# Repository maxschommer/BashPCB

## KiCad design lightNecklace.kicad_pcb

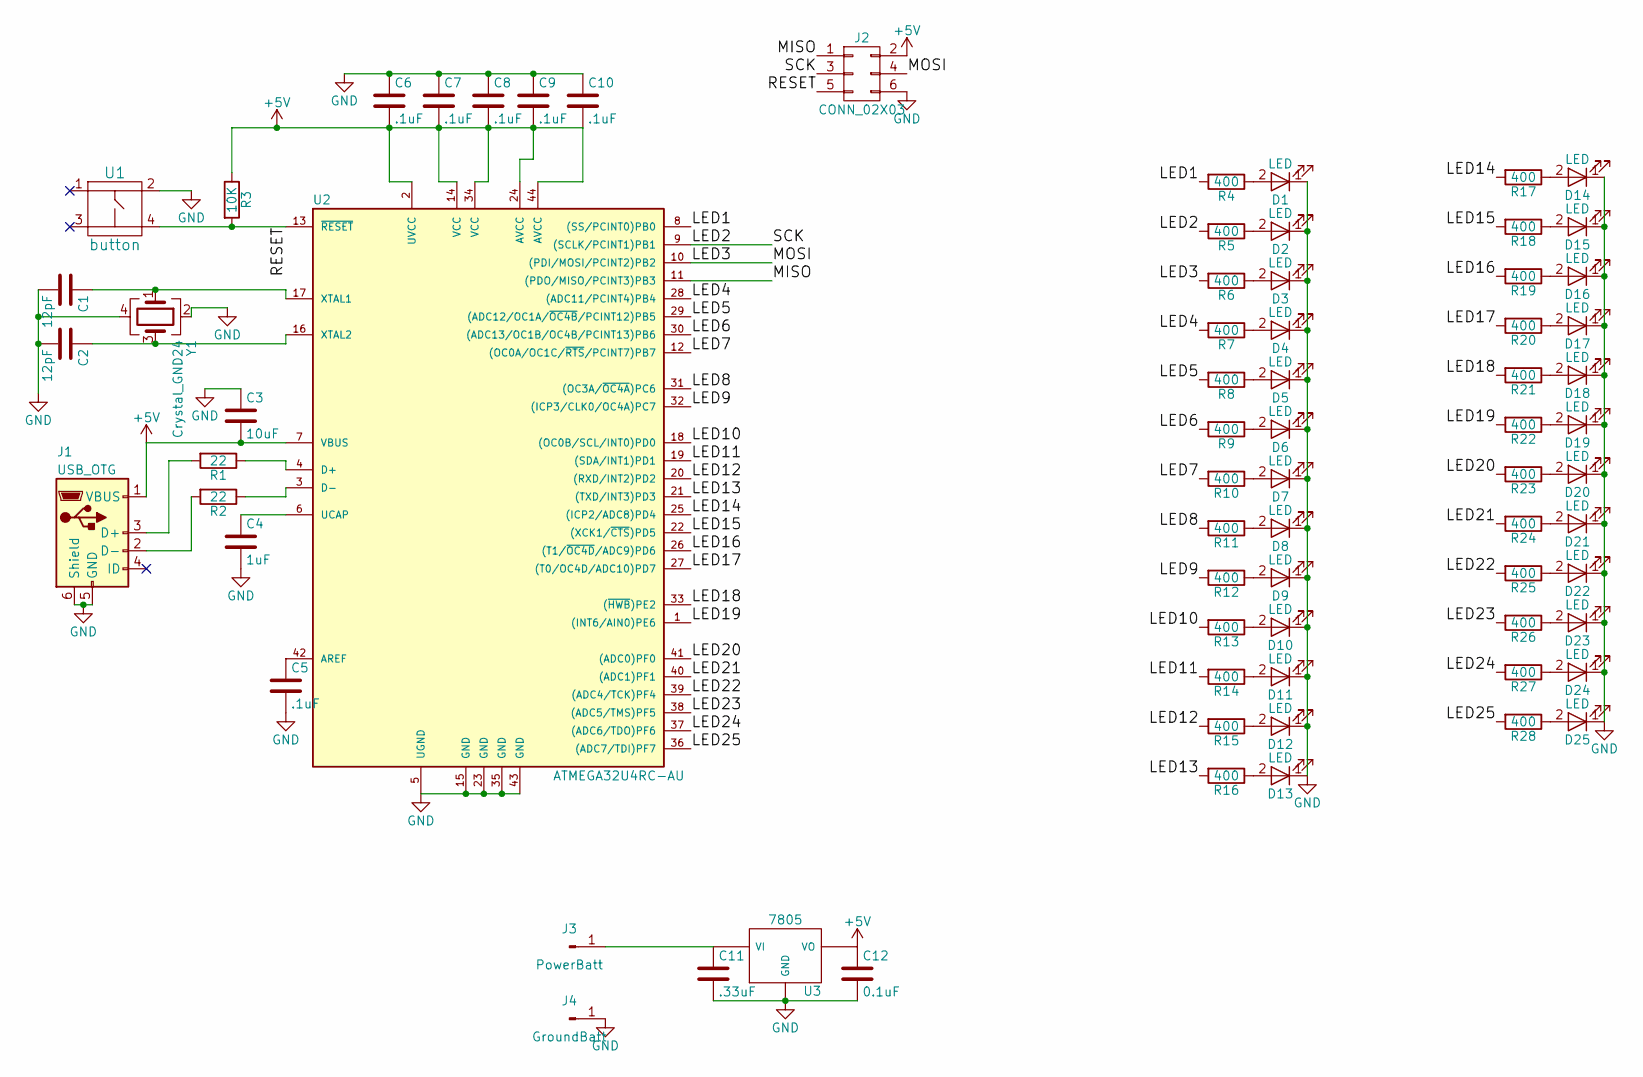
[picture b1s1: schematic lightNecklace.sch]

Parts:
C1, C2: 12pF; C_0603
C3: 10uF; C_0805
C4: 1uF; C_0603
C5, C6, C7, C8, C9, C10: .1uF; C_0603
C11: .33uF; C_0603
C12: 0.1uF; C_0603
D1, D2, D3, D4, D5, D6, D7, D8, D9, D10, D11, D12, D13, D14, D15, D16, D17, D18, D19, D20, D21, D22, D23, D24, D25: LED; LED_0805
J1: USB_OTG; USB_Micro-B
J2: CONN_02X03; Pin_Header_Straight_2x03_Pitch2.54mm_SMD
J3: PowerBatt; 1pin
J4: GroundBatt; 1pin
R1, R2: 22; R_0603
R3: 10K; R_0603
R4, R5, R6, R7, R8, R9, R10, R11, R12, R13, R14, R15, R16, R17, R18, R19, R20, R21, R22, R23, R24, R25, R26, R27, R28: 400; R_0603
U1: button; KMT071_NGJ_LHS
U2: ATMEGA32U4RC-AU; TQFP-44_10x10mm_Pitch0.8mm
U3: 7805; D2PAK
Y1: Crystal_GND24; Crystal_SMD_3225-4pin_3.2x2.5mm

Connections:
+5V: C3.2, C6.2, C7.2, C8.2, C9.2, C10.2, C12.1, J1.1 (VBUS), J2.2, R3.1, U2.2 (UVCC), U2.7 (VBUS), U2.14 (VCC), U2.24 (AVCC), U2.34 (VCC), U2.44 (AVCC), U3.VO
/LED1: R4.2, U2.8 ((SS/PCINT0)PB0)
/LED2: J2.3, R5.2, U2.9 ((SCLK/PCINT1)PB1)
/LED3: J2.4, R6.2, U2.10 ((PDI/MOSI/PCINT2)PB2)
/LED4: R7.2, U2.28 ((ADC11/PCINT4)PB4)
/LED5: R8.2, U2.29 ((ADC12/OC1A/~OC4B~/PCINT12)PB5)
/LED6: R9.2, U2.30 ((ADC13/OC1B/OC4B/PCINT13)PB6)
/LED7: R10.2, U2.12 ((OC0A/OC1C/~RTS~/PCINT7)PB7)
/LED8: R11.2, U2.31 ((OC3A/~OC4A~)PC6)
/LED9: R12.2, U2.32 ((ICP3/CLK0/OC4A)PC7)
/LED10: R13.2, U2.18 ((OC0B/SCL/INT0)PD0)
/LED11: R14.2, U2.19 ((SDA/INT1)PD1)
/LED12: R15.2, U2.20 ((RXD/INT2)PD2)
/LED13: R16.2, U2.21 ((TXD/INT3)PD3)
/LED14: R17.2, U2.25 ((ICP2/ADC8)PD4)
/LED15: R18.2, U2.22 ((XCK1/~CTS~)PD5)
/LED16: R19.2, U2.26 ((T1/~OC4D~/ADC9)PD6)
/LED17: R20.2, U2.27 ((T0/OC4D/ADC10)PD7)
/LED18: R21.2, U2.33 ((~HWB~)PE2)
/LED19: R22.2, U2.1 ((INT6/AIN0)PE6)
/LED20: R23.2, U2.41 ((ADC0)PF0)
/LED21: R24.2, U2.40 ((ADC1)PF1)
/LED22: R25.2, U2.39 ((ADC4/TCK)PF4)
/LED23: R26.2, U2.38 ((ADC5/TMS)PF5)
/LED24: R27.2, U2.37 ((ADC6/TDO)PF6)
/LED25: R28.2, U2.36 ((ADC7/TDI)PF7)
/MISO: J2.1, U2.11 ((PDO/MISO/PCINT3)PB3)
/RESET: J2.5, R3.2, U1.4, U2.13 (~RESET~)
GND: C1.2, C2.2, C3.1, C4.2, C5.2, C6.1, C7.1, C8.1, C9.1, C10.1, C11.2, C12.2, D1.1 (K), D2.1 (K), D3.1 (K), D4.1 (K), D5.1 (K), D6.1 (K), D7.1 (K), D8.1 (K), D9.1 (K), D10.1 (K), D11.1 (K), D12.1 (K), D13.1 (K), D14.1 (K), D15.1 (K), D16.1 (K), D17.1 (K), D18.1 (K), D19.1 (K), D20.1 (K), D21.1 (K), D22.1 (K), D23.1 (K), D24.1 (K), D25.1 (K), J1.5 (GND), J1.6 (Shield), J2.6, J4.1, U1.2, U2.5 (UGND), U2.15 (GND), U2.23 (GND), U2.35 (GND), U2.43 (GND), U3.GND, Y1.2, Y1.4
unnamed: C1.1, U2.17 (XTAL1), Y1.1
unnamed: C2.1, U2.16 (XTAL2), Y1.3
unnamed: C4.1, U2.6 (UCAP)
unnamed: C5.1, U2.42 (AREF)
unnamed: C11.1, J3.1, U3.VI
unnamed: D1.2 (A), R4.1
unnamed: D2.2 (A), R5.1
unnamed: D3.2 (A), R6.1
unnamed: D4.2 (A), R7.1
unnamed: D5.2 (A), R8.1
unnamed: D6.2 (A), R9.1
unnamed: D7.2 (A), R10.1
unnamed: D8.2 (A), R11.1
unnamed: D9.2 (A), R12.1
unnamed: D10.2 (A), R13.1
unnamed: D11.2 (A), R14.1
unnamed: D12.2 (A), R15.1
unnamed: D13.2 (A), R16.1
unnamed: D14.2 (A), R17.1
unnamed: D15.2 (A), R18.1
unnamed: D16.2 (A), R19.1
unnamed: D17.2 (A), R20.1
unnamed: D18.2 (A), R21.1
unnamed: D19.2 (A), R22.1
unnamed: D20.2 (A), R23.1
unnamed: D21.2 (A), R24.1
unnamed: D22.2 (A), R25.1
unnamed: D23.2 (A), R26.1
unnamed: D24.2 (A), R27.1
unnamed: D25.2 (A), R28.1
unnamed: J1.2 (D-), R2.2
unnamed: J1.3 (D+), R1.2
unnamed: R1.1, U2.4 (D+)
unnamed: R2.1, U2.3 (D-)

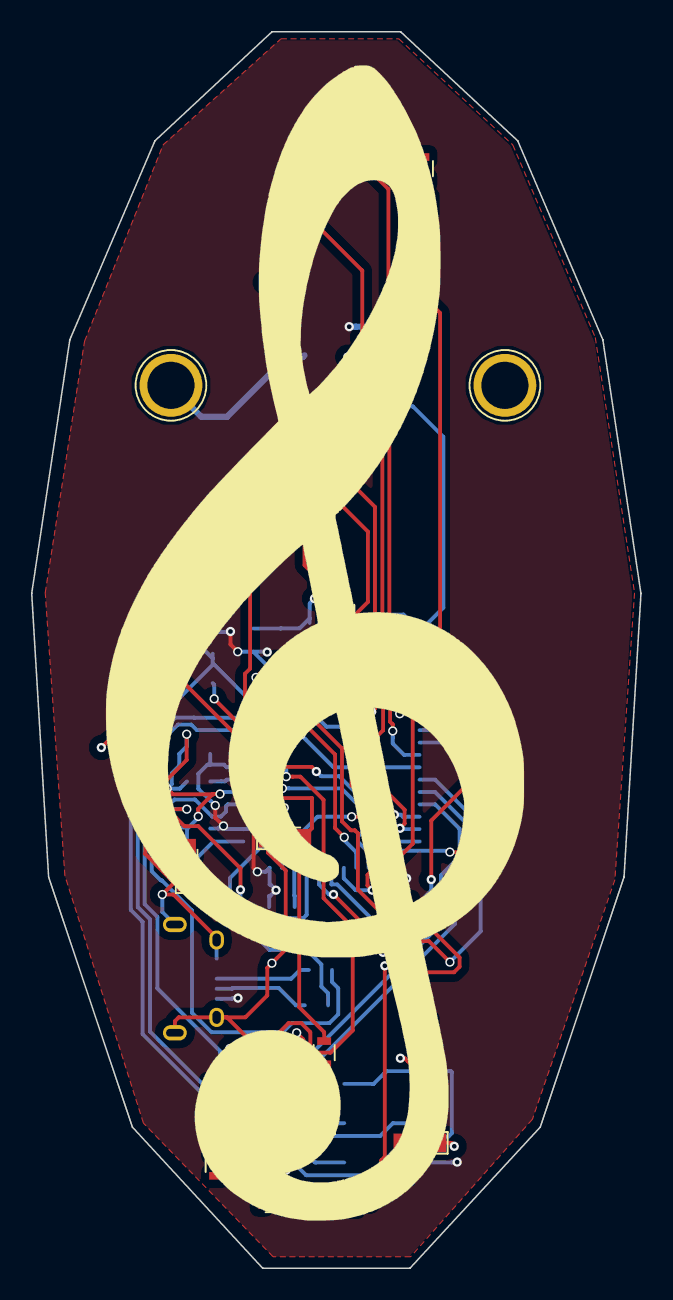
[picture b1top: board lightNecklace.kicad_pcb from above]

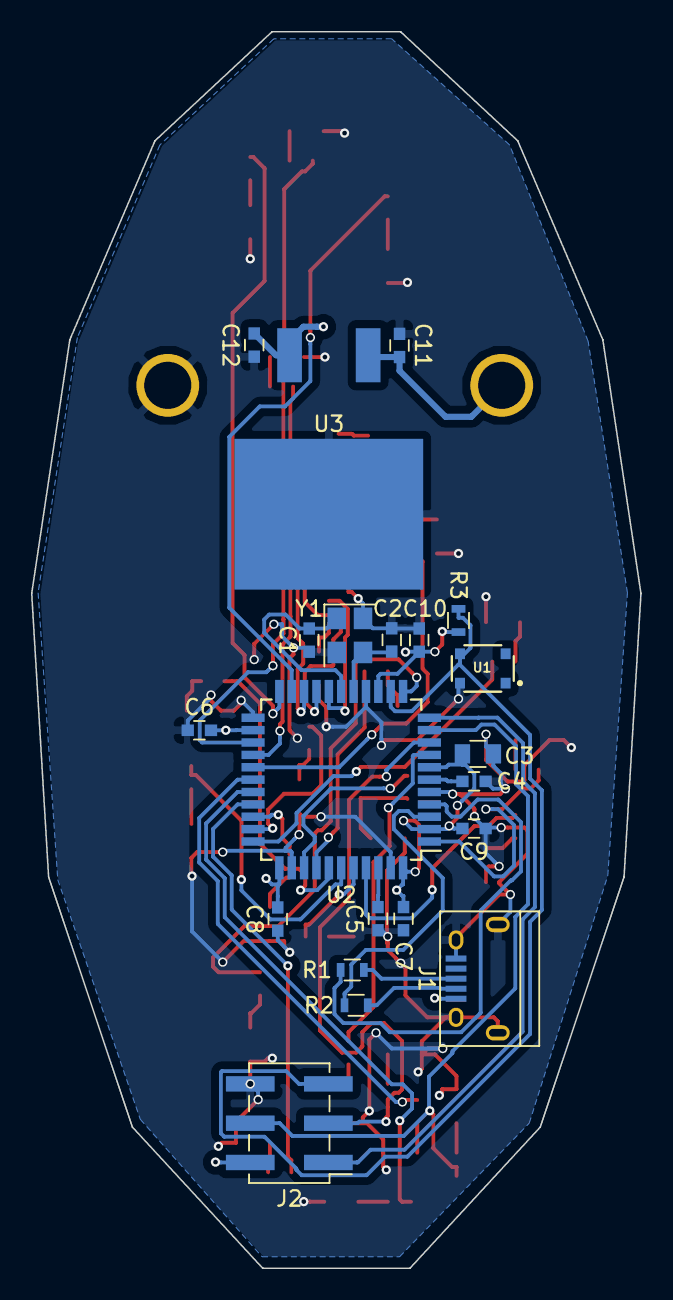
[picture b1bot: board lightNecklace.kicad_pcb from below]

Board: 2 copper layers, 39.4 x 79.9 mm, 73 parts (21 on the bottom side), 63 nets.

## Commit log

2017-12-22 Finished schematic
2017-12-22 Added treble cleff
2017-12-22 Added button lib
2017-12-22 Finished CVPCB
2017-12-22 Added button footprint
2017-12-22 Fixed file location
2017-12-23 Made edge cuts
2017-12-23 Finished Board
